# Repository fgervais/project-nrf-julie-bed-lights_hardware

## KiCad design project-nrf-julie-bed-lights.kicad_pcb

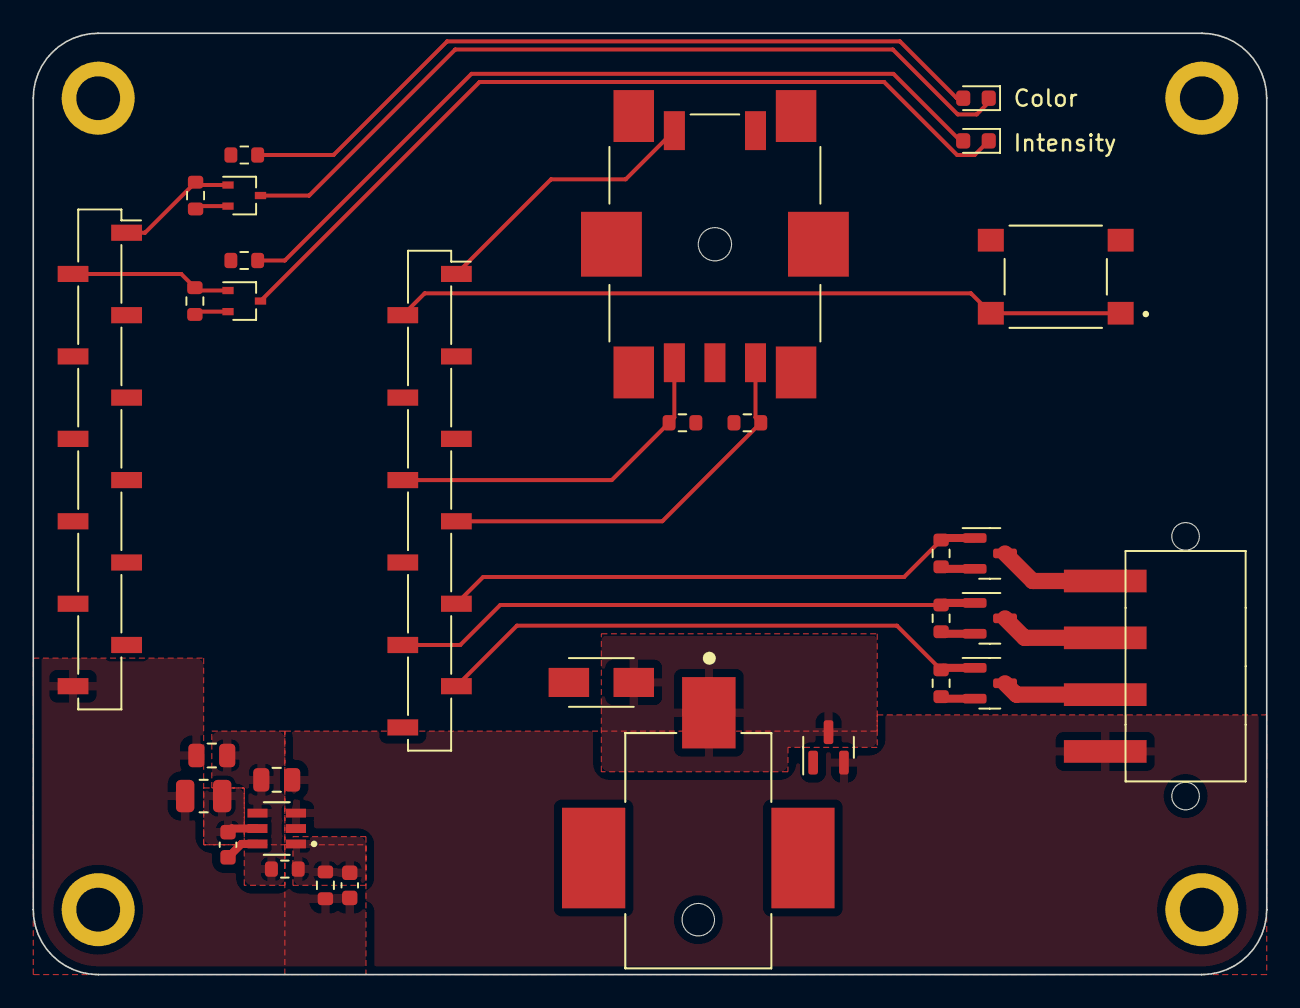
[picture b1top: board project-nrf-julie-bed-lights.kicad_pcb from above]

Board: 2 copper layers, 76.0 x 58.0 mm, 36 parts (0 on the bottom side), 23 nets.

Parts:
C1: 10uF; C_0805_2012Metric
C2: 22uF; C_0805_2012Metric
C3: 100nF; C_0603_1608Metric
C4: 56pF; C_0603_1608Metric
D1: Color; LED_0603_1608Metric
D2: Intensity; LED_0603_1608Metric
D3: SMAJ12CA-13-F; D_SMA
H1, H2, H3, H4: MountingHole_Pad; MountingHole_2.7mm_M2.5_ISO7380_Pad
J1: PJ-036AH-SMT-TR; CUI_PJ-036AH-SMT-TR
J2: Screw_Terminal_01x04; TZ042101B000G
J3: Left; PinSocket_1x12_P2.54mm_Vertical_SMD_Pin1Right
J4: Right; PinSocket_1x12_P2.54mm_Vertical_SMD_Pin1Right
L1: 10uH; INDC2518X200N
Q1, Q2, Q3: Si231BDS; SOT-23
Q4, Q5: RU1J002YN; SOT-323_SC-70
Q6: PJA3441_R1_00001; SOT-23
R1: 82.5k; R_0603_1608Metric
R2: 30.1k; R_0603_1608Metric
R3, R4, R5, R6, R8, R10, R11: 10k; R_0603_1608Metric
R7, R9: 1k; R_0603_1608Metric
S1: Change mode; SW_B3FS-1010P
SW1: Change value; PEC11S-9213K-S0015
U1: AP63300WU-7; SOT95P280X100-6N

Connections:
+3V0: C2.1, C4.1, J3.12, L1.2, R1.1, R7.1, R9.1, R10.1, R11.1
+12V: C1.1, J2.1, Q6.2 (S), U1.2 (EN), U1.3 (VIN)
/Bleu: J2.2, Q1.3 (D)
/Bleu_PWM: J4.11, Q1.1 (G), R3.1
/Color_LED: J3.1, Q4.1 (G), R6.1
/Encoder_Button: J4.1, SW1.S1
/External_Button: J4.2, S1.1
/Intensity_LED: J3.2, Q5.1 (G), R8.1
/PhaseA: J4.6, R11.2, SW1.A
/PhaseB: J4.7, R10.2, SW1.B
/Rouge: J2.3, Q2.3 (D)
/Rouge_PWM: J4.10, Q2.1 (G), R4.1
/Vert: J2.4, Q3.3 (D)
/Vert_PWM: J4.9, Q3.1 (G), R5.1
GND: C1.2, C2.2, D3.1 (A1), H1.1, H2.1, H3.1, H4.1, J1.2, J4.12, Q1.2 (S), Q2.2 (S), Q3.2 (S), Q4.2 (S), Q5.2 (S), Q6.1 (G), R2.2, R3.2, R4.2, R5.2, R6.2, R8.2, S1.2, SW1.C, SW1.S2, U1.4 (GND)
unnamed: C3.1, L1.1, U1.5 (SW)
unnamed: C3.2, U1.6 (BST)
unnamed: C4.2, R1.2, R2.1, U1.1 (FB)
unnamed: D1.1 (K), Q4.3 (D)
unnamed: D1.2 (A), R7.2
unnamed: D2.1 (K), Q5.3 (D)
unnamed: D2.2 (A), R9.2
VCC: D3.2 (A2), J1.1, Q6.3 (D)

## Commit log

2023-01-02 Add black kicad project
2023-01-02 Add parts to schematic
    From rev2,v2 plan
2023-01-02 Ignore backups
2023-01-02 Add mounting holes and female sockets
2023-01-06 Half the schematic ready
2023-01-07 Add the pink_panda sub-sheet
2023-01-08 Connect everything to the panda board
2023-01-08 Add an ap63300 sheet
2023-01-08 Add separations in main sheet
2023-01-08 Add NCs to MCU
2023-01-08 Annotate
2023-01-08 Fix schematic errors
2023-01-13 Add input protection
2023-01-15 Import parts to pcb
2023-01-17 Add pull-ups to the rotary encoder
2023-01-17 Update board
2023-02-14 About half placement
2023-02-17 Everything placed except step-down
2023-02-17 First complete placement done
2023-02-19 Routing except power done
